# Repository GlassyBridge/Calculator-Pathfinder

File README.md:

# Calculator-Pathfinder
My submission for Pathfinder at hackclub.
Has 4 keys for inputs and LEDs + OLED for display. Uses XIAO microcontroller.
I'm thinking of using it to make a calculator now but it should be customizable.

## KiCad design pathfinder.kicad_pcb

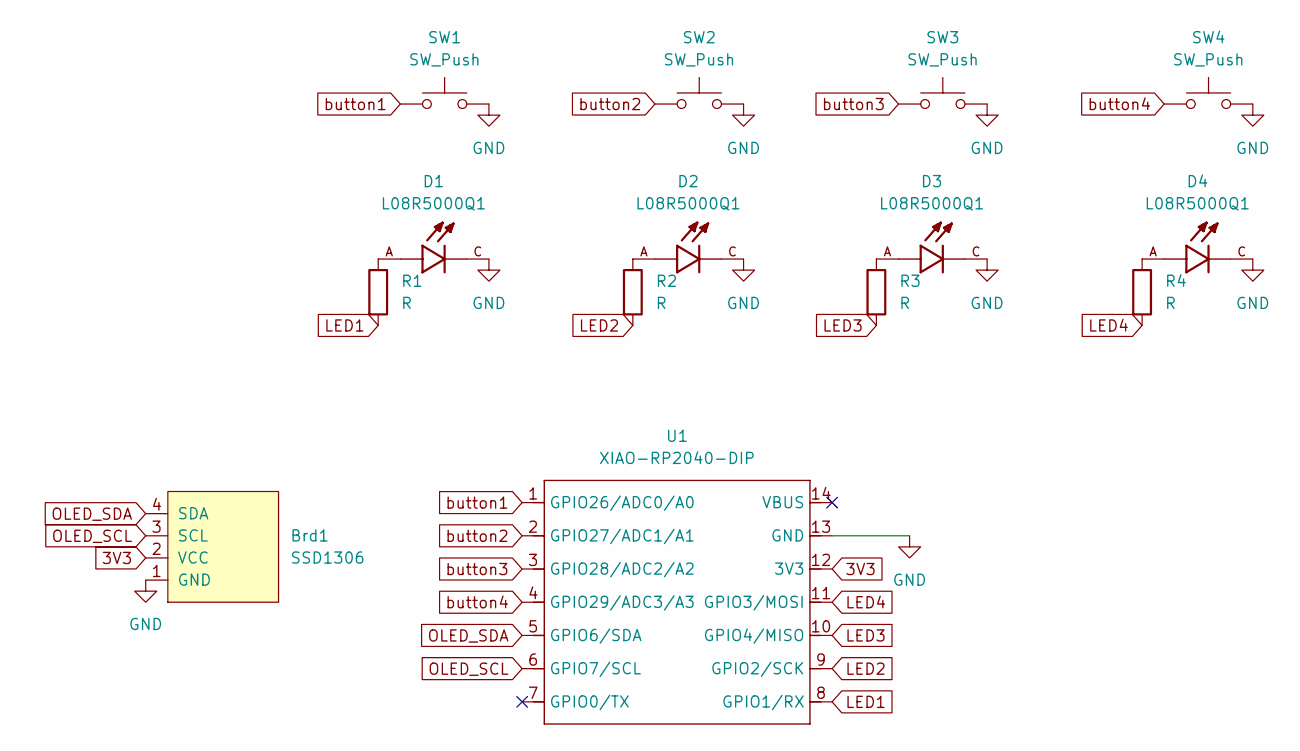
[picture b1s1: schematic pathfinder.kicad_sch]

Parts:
Brd1: SSD1306; 128x64OLED
D1, D2, D3, D4: L08R5000Q1; LEDRD254W57D500H1070; PARTREV NA
R1, R2, R3, R4: R; R_Axial_DIN0204_L3.6mm_D1.6mm_P5.08mm_Horizontal
SW1, SW2, SW3, SW4: SW_Push; SW_Cherry_MX_1.00u_PCB
U1: XIAO-RP2040-DIP

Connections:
3V3: Brd1.2 (VCC), U1.12 (3V3)
GND: Brd1.1 (GND), D1.C, D2.C, D3.C, D4.C, SW1.2, SW2.2, SW3.2, SW4.2, U1.13 (GND)
LED1: R1.2, U1.8 (GPIO1/RX)
LED2: R2.2, U1.9 (GPIO2/SCK)
LED3: R3.2, U1.10 (GPIO4/MISO)
LED4: R4.2, U1.11 (GPIO3/MOSI)
unnamed: D1.A, R1.1
unnamed: D2.A, R2.1
unnamed: D3.A, R3.1
unnamed: D4.A, R4.1
OLED_SCL: Brd1.3 (SCL), U1.6 (GPIO7/SCL)
OLED_SDA: Brd1.4 (SDA), U1.5 (GPIO6/SDA)
button1: SW1.1, U1.1 (GPIO26/ADC0/A0)
button2: SW2.1, U1.2 (GPIO27/ADC1/A1)
button3: SW3.1, U1.3 (GPIO28/ADC2/A2)
button4: SW4.1, U1.4 (GPIO29/ADC3/A3)

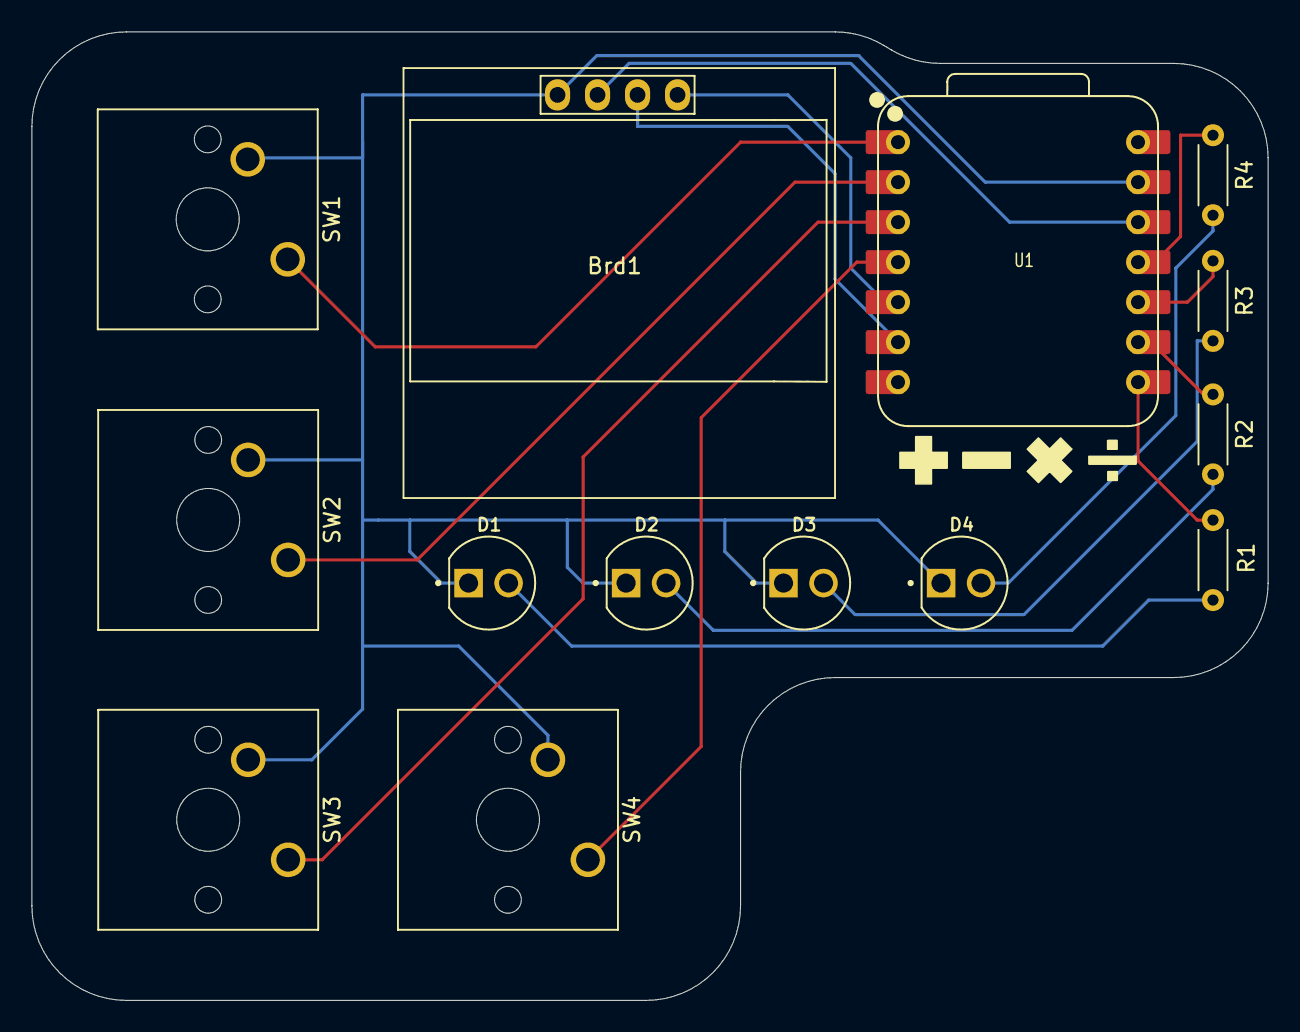
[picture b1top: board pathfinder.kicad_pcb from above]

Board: 2 copper layers, 78.5 x 61.5 mm, 14 parts (0 on the bottom side), 16 nets.

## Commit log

2025-07-30 Initial upload
